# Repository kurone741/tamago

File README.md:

# tamago

tamago is a simple desktop companion. I built it because I thought it seemed like a good entry point into pcb design, without being unnecessarily complex. 

Functionality includes date/time, timer, stopwatch, countdown, and noise visualizer which responds to the sounds in your working space (e.g. typing/music). It can also display humidity and temperature of your working space. It's a device that is for the most part single-purpose, meaning it doesn't occupy more of your attention than it needs. THis also helps me stay on focus more.

ps. tamago is japanese for egg

## bill of materials
| Item | Qty | Supplier | Cost/item | Total Cost | Link |
|---|---:|---|---:|---:|---|
| ESP32-C3-MINI-1 | 1 | Aliexpress | $4.69 | $4.69 | https://www.aliexpress.com/item/3256810385497528.html |
| 0.96" OLED | 1 | Aliexpress | $1.09 | $1.09 | https://www.aliexpress.com/item/3256810476428595.html |
| EC11 KY-040 Rotary Encoder | 1 | Aliexpress | $2.49 | $2.49 | https://www.aliexpress.com/item/3256812187820082.html |
| DHT11 | 1 | Aliexpress | $2.01 | $2.01 | https://www.aliexpress.com/item/3256808804649487.html |
| INMP441 | 1 | Aliexpress | $2.95 | $2.95 | https://www.aliexpress.com/item/3256809519855925.html |
| Passive Components | 1 | Aliexpress | $12.27 | $12.27 | https://www.aliexpress.us/item/3256803146822180.html |
| PCB | 1 | JLCPCB | $4.00 | $4.00 | https://jlcpcb.com |
| Estimated total shipping | 1 | | | $0.00 | |

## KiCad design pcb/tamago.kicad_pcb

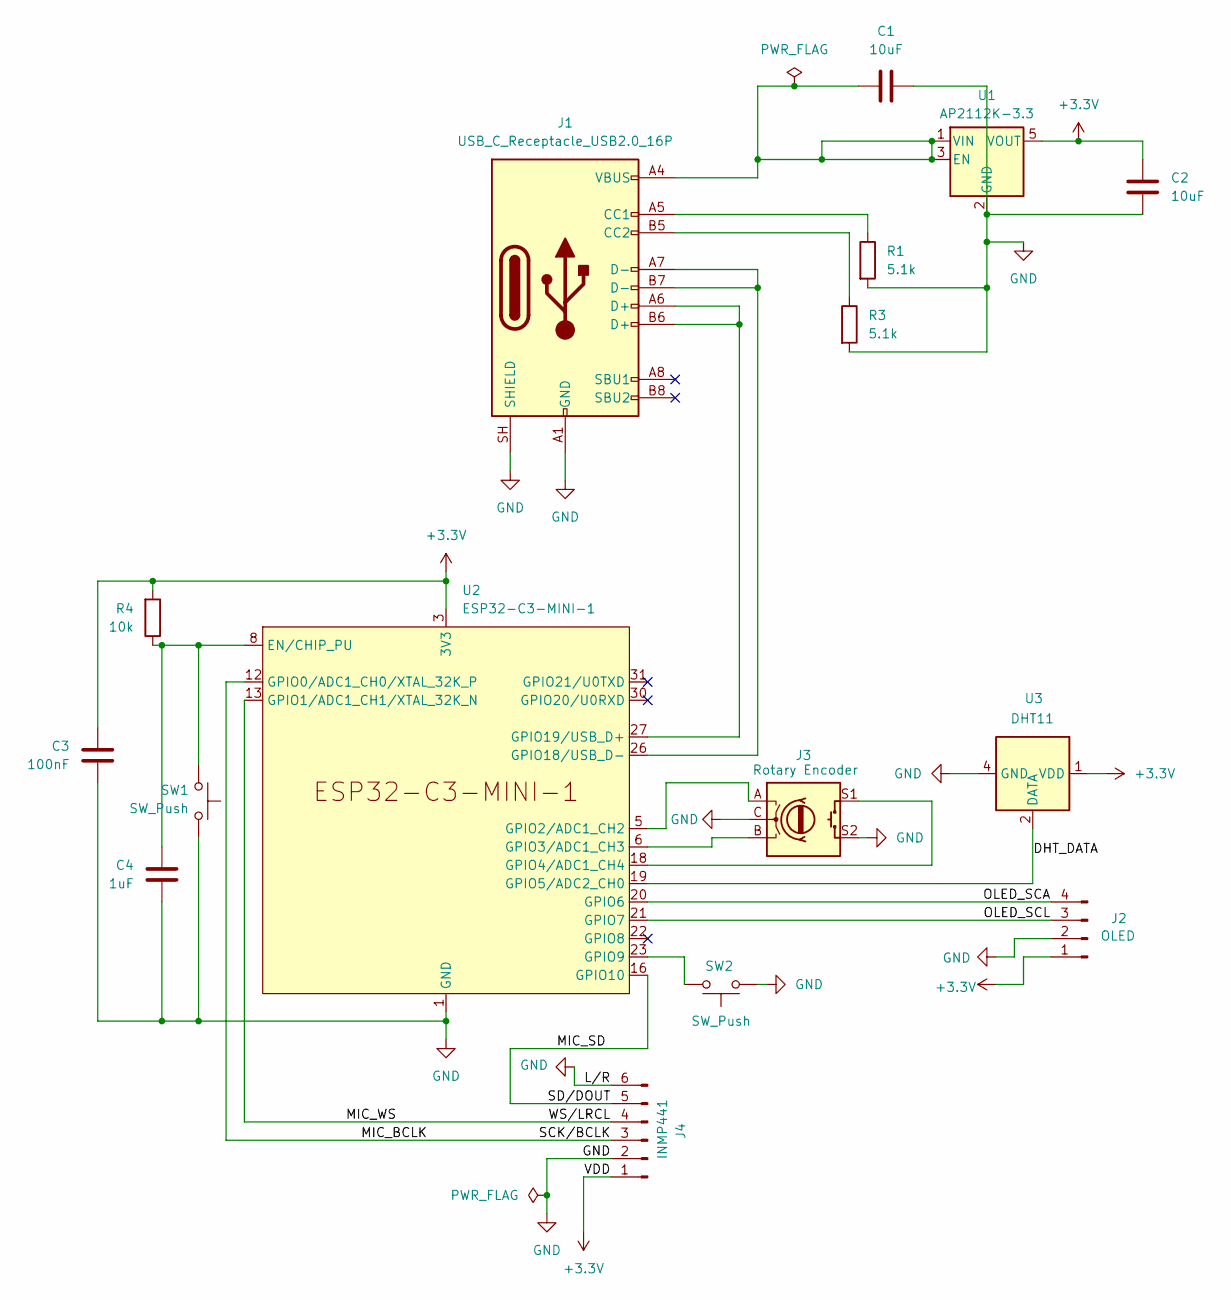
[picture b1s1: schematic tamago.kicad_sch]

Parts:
C1, C2: 10uF; C_0805_2012Metric_Pad1.18x1.45mm_HandSolder
C3: 100nF; C_0805_2012Metric_Pad1.18x1.45mm_HandSolder
C4: 1uF; C_0805_2012Metric_Pad1.18x1.45mm_HandSolder
J1: USB_C_Receptacle_USB2.0_16P; USB_C_Receptacle_HRO_TYPE-C-31-M-12
J2: OLED; Adafruit_SSD1306_No_Mounting_Holes
J3: Rotary Encoder; RotaryEncoder_Alps_EC11E-Switch_Vertical_H20mm
J4: INMP441; PinHeader_1x06_P2.54mm_Vertical
R1, R3: 5.1k; R_0805_2012Metric_Pad1.20x1.40mm_HandSolder
R4: 10k; R_0805_2012Metric_Pad1.20x1.40mm_HandSolder
SW1, SW2: SW_Push; SW_PUSH_6mm
U1: AP2112K-3.3; SOT-23-5
U2: ESP32-C3-MINI-1
U3: DHT11; Aosong_DHT11_5.5x12.0_P2.54mm

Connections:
+3.3V: C2.1, C3.1, J2.1, J4.1, R4.2, U1.5 (VOUT), U2.3 (3V3), U3.1 (VDD)
/DHT_DATA: U2.19 (GPIO5/ADC2_CH0), U3.2 (DATA)
/MIC_BCLK: J4.3, U2.12 (GPIO0/ADC1_CH0/XTAL_32K_P)
/MIC_SD: J4.5, U2.16 (GPIO10)
/MIC_WS: J4.4, U2.13 (GPIO1/ADC1_CH1/XTAL_32K_N)
/OLED_SCA: J2.4, U2.20 (GPIO6)
/OLED_SCL: J2.3, U2.21 (GPIO7)
GND: C1.1, C2.2, C3.2, C4.2, J1.A1 (GND), J1.A12 (GND), J1.B1 (GND), J1.B12 (GND), J1.SH (SHIELD), J2.2, J3.C, J3.S2, J4.2, J4.6, R1.2, R3.2, SW1.1, SW2.2, U1.2 (GND), U2.1 (GND), U2.2 (GND), U2.11 (GND), U2.14 (GND), U2.36 (GND), U2.37 (GND), U2.38 (GND), U2.39 (GND), U2.40 (GND), U2.41 (GND), U2.42 (GND), U2.43 (GND), U2.44 (GND), U2.45 (GND), U2.46 (GND), U2.47 (GND), U2.48 (GND), U2.49 (GND), U2.50 (GND), U2.51 (GND), U2.52 (GND), U2.53 (GND), U3.4 (GND)
unnamed: J1.A5 (CC1), R1.1
unnamed: J1.B5 (CC2), R3.1
unnamed: C1.2, J1.A4 (VBUS), J1.A9 (VBUS), J1.B4 (VBUS), J1.B9 (VBUS), U1.1 (VIN), U1.3 (EN)
unnamed: C4.1, R4.1, SW1.2, U2.8 (EN/CHIP_PU)
unnamed: J3.A, U2.5 (GPIO2/ADC1_CH2)
unnamed: J3.B, U2.6 (GPIO3/ADC1_CH3)
unnamed: J3.S1, U2.18 (GPIO4/ADC1_CH4)
unnamed: SW2.1, U2.23 (GPIO9)
unnamed: J1.A7 (D-), J1.B7 (D-), U2.26 (GPIO18/USB_D-)
unnamed: J1.A6 (D+), J1.B6 (D+), U2.27 (GPIO19/USB_D+)

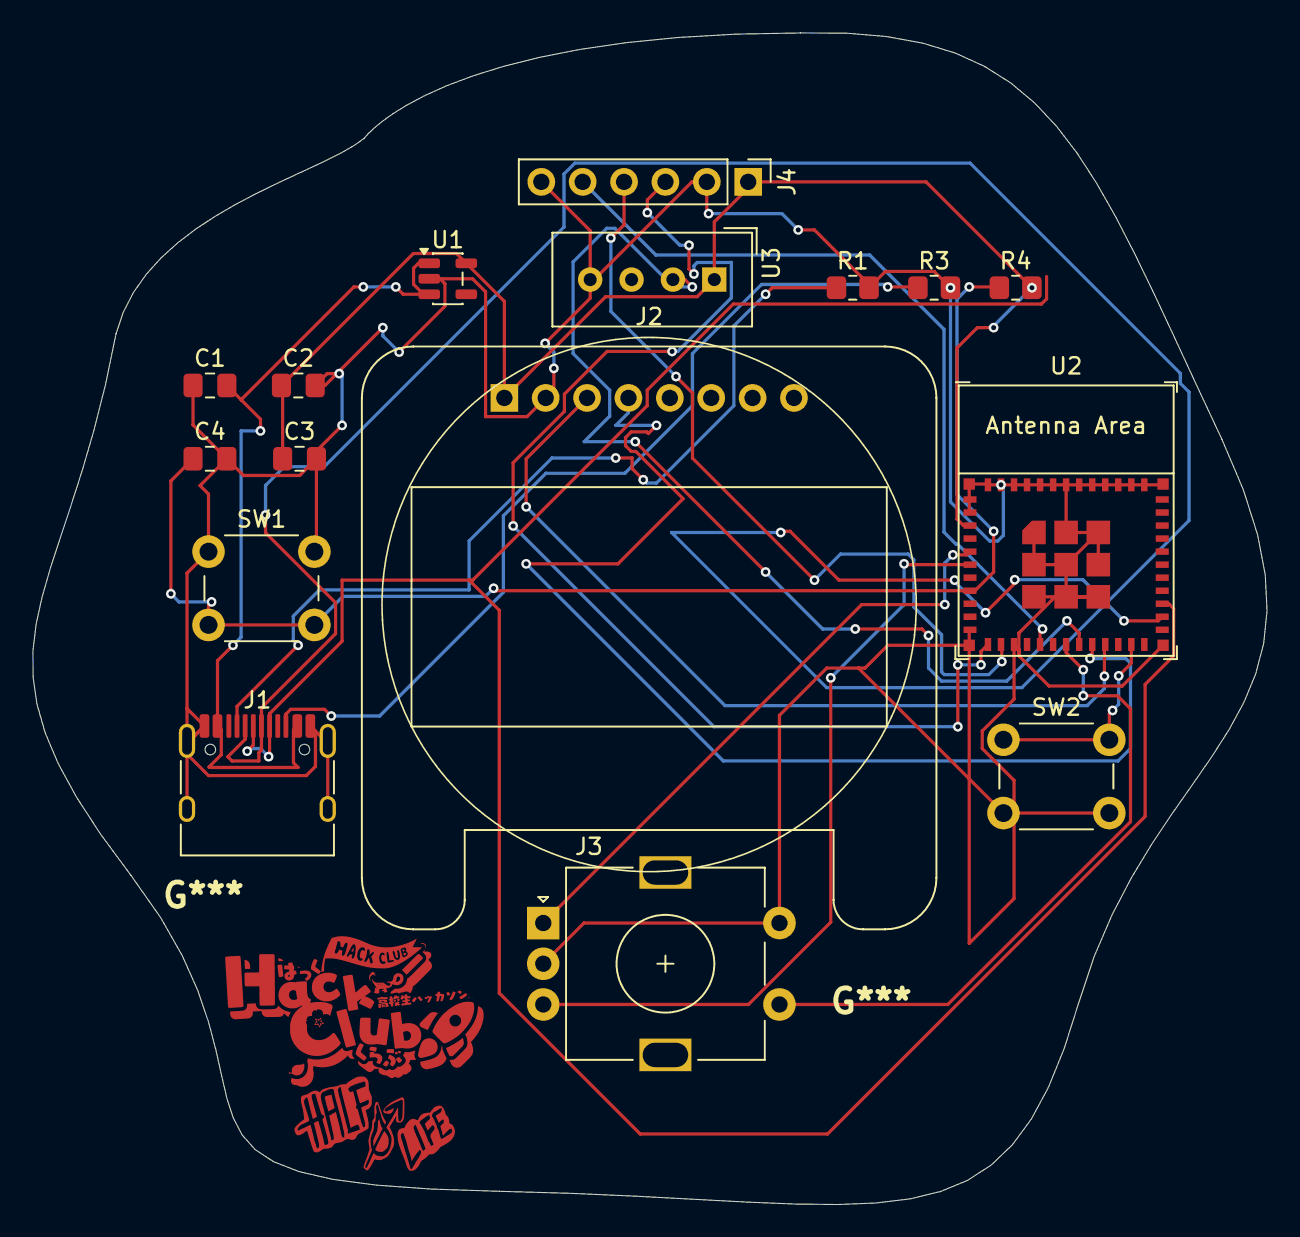
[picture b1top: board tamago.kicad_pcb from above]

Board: 2 copper layers, 75.8 x 71.9 mm, 16 parts (0 on the bottom side), 18 nets.

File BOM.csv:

"Reference","Qty","Value","DNP","Exclude from BOM","Exclude from Board","Exclude from Simulation","Exclude from Position Files","Footprint","Datasheet"
"C1,C2","2","10uF","","","","","${EXCLUDE_FROM_POS_FILES}","Capacitor_SMD:C_0805_2012Metric_Pad1.18x1.45mm_HandSolder",""
"C3","1","100nF","","","","","${EXCLUDE_FROM_POS_FILES}","Capacitor_SMD:C_0805_2012Metric_Pad1.18x1.45mm_HandSolder",""
"C4","1","1uF","","","","","${EXCLUDE_FROM_POS_FILES}","Capacitor_SMD:C_0805_2012Metric_Pad1.18x1.45mm_HandSolder",""
"J1","1","USB_C_Receptacle_USB2.0_16P","","","","","${EXCLUDE_FROM_POS_FILES}","Connector_USB:USB_C_Receptacle_HRO_TYPE-C-31-M-12","https://www.usb.org/sites/default/files/documents/usb_type-c.zip"
"J2","1","OLED","","","","","${EXCLUDE_FROM_POS_FILES}","Display:Adafruit_SSD1306_No_Mounting_Holes",""
"J3","1","Rotary Encoder","","","","","${EXCLUDE_FROM_POS_FILES}","Rotary_Encoder:RotaryEncoder_Alps_EC11E-Switch_Vertical_H20mm",""
"J4","1","INMP441","","","","","${EXCLUDE_FROM_POS_FILES}","Connector_PinHeader_2.54mm:PinHeader_1x06_P2.54mm_Vertical",""
"R1,R3","2","5.1k","","","","","${EXCLUDE_FROM_POS_FILES}","Resistor_SMD:R_0805_2012Metric_Pad1.20x1.40mm_HandSolder",""
"R4","1","10k","","","","","${EXCLUDE_FROM_POS_FILES}","Resistor_SMD:R_0805_2012Metric_Pad1.20x1.40mm_HandSolder",""
"SW1,SW2","2","SW_Push","","","","","${EXCLUDE_FROM_POS_FILES}","Button_Switch_THT:SW_PUSH_6mm",""
"U1","1","AP2112K-3.3","","","","","${EXCLUDE_FROM_POS_FILES}","Package_TO_SOT_SMD:SOT-23-5","https://www.diodes.com/assets/Datasheets/AP2112.pdf"
"U2","1","ESP32-C3-MINI-1","","","","","${EXCLUDE_FROM_POS_FILES}","PCM_Espressif:ESP32-C3-MINI-1","https://www.espressif.com/sites/default/files/documentation/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"
"U3","1","DHT11","","","","","${EXCLUDE_FROM_POS_FILES}","Sensor:Aosong_DHT11_5.5x12.0_P2.54mm","http://akizukidenshi.com/download/ds/aosong/DHT11.pdf"

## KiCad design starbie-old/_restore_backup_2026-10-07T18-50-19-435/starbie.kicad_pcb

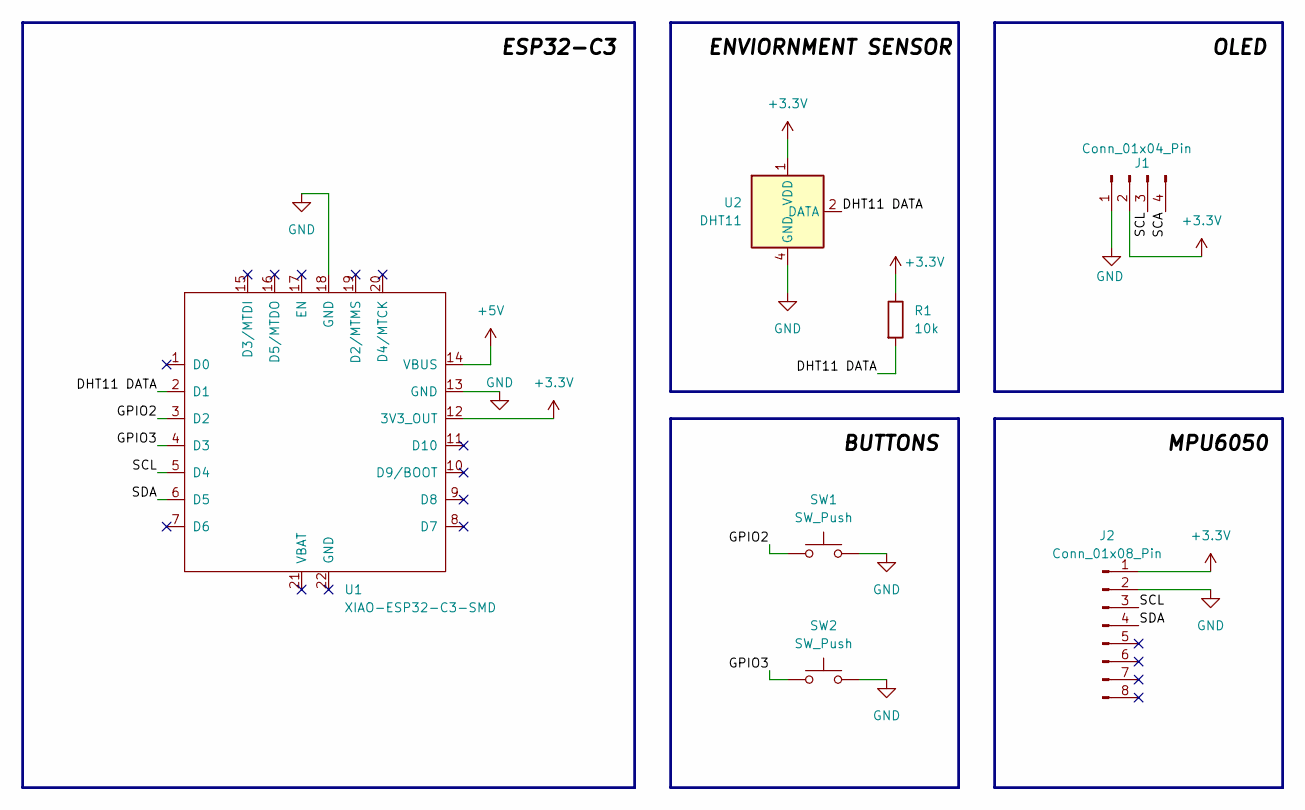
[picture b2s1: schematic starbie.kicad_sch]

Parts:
J1: Conn_01x04_Pin; Display_128x64_096_I2C
J2: Conn_01x08_Pin; PinHeader_1x08_P2.54mm_Vertical
R1: 10k; R_Axial_DIN0204_L3.6mm_D1.6mm_P7.62mm_Horizontal
SW1, SW2: SW_Push; SW_Cherry_MX_1.00u_PCB
U1: XIAO-ESP32-C3-SMD
U2: DHT11; Aosong_DHT11_5.5x12.0_P2.54mm

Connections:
+3.3V: J1.2, J2.1, R1.1, U1.12 (3V3_OUT), U2.1 (VDD)
+5V: U1.14 (VBUS)
/DHT11 DATA: R1.2, U1.2 (D1), U2.2 (DATA)
/GPIO2: SW1.1, U1.3 (D2)
/GPIO3: SW2.1, U1.4 (D3)
/SCA: J1.4
/SCL: J1.3, J2.3, U1.5 (D4)
/SDA: J2.4, U1.6 (D5)
GND: J1.1, J2.2, SW1.2, SW2.2, U1.13 (GND), U1.18 (GND), U2.4 (GND)

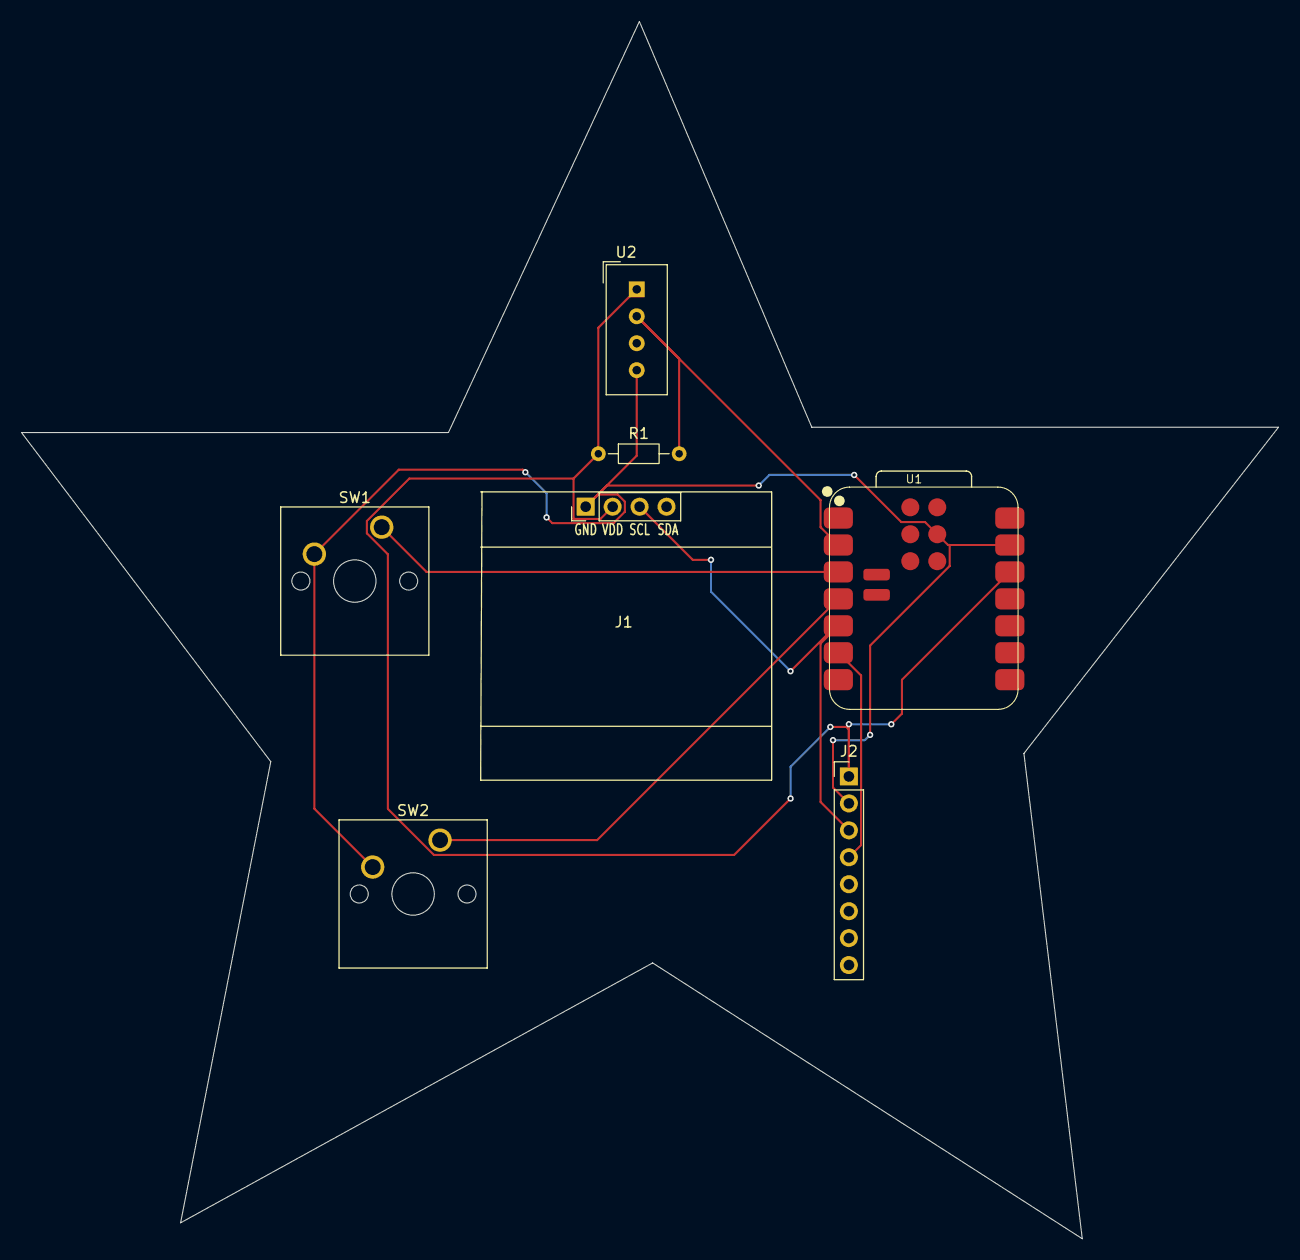
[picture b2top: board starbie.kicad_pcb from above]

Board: 2 copper layers, 118.5 x 114.8 mm, 7 parts (0 on the bottom side), 7 nets.
